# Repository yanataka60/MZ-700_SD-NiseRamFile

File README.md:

# MZ-700_SD+偽RAMFILE複合ボード

　しっぽいいんちょさんが作られた「偽RAMFILE for MZ-1500」を元にしてMZ-700_SDを合体させたボードです。

　オマケとしてMZ-1500のサウンド機能を付加してMZ-1500用ゲームのサウンドも鳴るようにしてみました。あくまでオマケですので完全にMZ-1500と同等になるかは未検証です。

#### 2026.4.17 Rev1.2の回路中LPFのコンデンサの位置に誤りがありました。後述「Rev1.2回路の修正」によりコンデンサの位置を修正してください。

#### 2026.4.25 Rev1.5以降では回路・基板改善しています。Rev1.2基板の場合のみ、後述「Rev1.2回路の修正」によりコンデンサの位置を修正してください。

#### 2026.6.21 MZ-700_SD+偽RAMFILE複合ボードに電源が供給されている状態でUSB-Cケーブルを接続してはいけない問題に対してRev1.6基板ではすーぱーたーぼさんからご指摘いただいた対策を施しました。Rev1.2、Rev1.5基板でも通常の使用でMZ-700_SD+偽RAMFILE複合ボードに電源が供給されている状態でUSB-Cケーブルを接続することはありませんので通常使用においてRev1.2、Rev1.5基板でも問題ありません。

　以下の機能があります。

・MZ-700_SDの起動及びMZ-700_SDの機能

・EMM0からの起動(ただし、EMM0にHu-BASICの起動ディスクイメージがある場合のみ)

・EMM0エミュレータ(320KByte)

・漢字ROMボードエミュレータ

・MZ-700のテキスト出力をエミュレートしてVGA出力

・VGA出力される出力にMZ-1500相当のPCG機能、パレット機能

・VGA出力される出力にPCG-700相当のPCG機能

・MZ-1500相当のサウンドエミュレート(SN76489x2、8253)

・EXT-ROM領域(E800h～FFFFh)のRAM化(起動時にはF000h～FFFFhにMZ-700_SD用ROMの内容が自動的に書き込まれます。1Z-009B_LauncherをLOAD起動後であればEXT-ROMをファイル化したEXT-ROM.MZTをEXT-ROM領域にLOADが可能です)

MZ-700_SD: https://github.com/yanataka60/MZ-700_SD

　「偽RAMFILE for MZ-1500」にはMZ-1R12 SRAMメモリエミュレータの機能がありますが、MZ-700_SDの起動用に使用しているのでMZ-1R12 SRAMメモリエミュレータとしての機能は使用できません。

　なおこの基板は、しっぽいいんちょさんの「偽1500 for MZ-700」のnise1500.uf2を書き込めば「偽1500 for MZ-700」になります。

　「偽1500 for MZ-700」とはフラッシュROMの使い方が違いますのでuf2ファイルを書き込んだときはそれぞれの説明に従ったフラッシュROMへの書込みを行ってください。

偽1500 for MZ-700:https://github.com/shippoiincho/nise1500

### (2026.8.13追記)すねいるさんのBARYONに対応するためArduinoプログラムを更新しました。また、ROMプログラムも合わせて更新することで多段ロードにも対応します。

### 多段ロードの詳細についてはMZ-80K_SDの「BARYON対応」「多段ロード対応」を参照してください。

　BARYON対応:https://github.com/yanataka60/MZ80K_SD#baryon%E5%AF%BE%E5%BF%9C2026813

　多段ロード対応:https://github.com/yanataka60/MZ80K_SD#%E5%A4%9A%E6%AE%B5%E3%83%AD%E3%83%BC%E3%83%89%E5%AF%BE%E5%BF%9C2026813

　Arduinoプログラム、ROMプログラムともMZ-80K_SD用に更新したものがそのまま使えます。

### BARYON起動時にE800h以降にも書き込み動作を行うようです。MZ-80K_SD、MZ-700_SDでは問題ありませんが、MZ-700_SD+偽RAMFILE複合ボードではE800h以降もRAM扱いとしていたため、SDアクセスルーチンが破壊されてしまいます。

### 当面、E800h以降はROM扱いに変更しましたのでRP2350Bフォルダにあるniseramfile.uf2でRP2350Bマイコンボードを書き換えてください。

## 回路図
　KiCadフォルダ内のMZ-700_SD+NRF.pdfを参照してください。

[回路図](https://github.com/yanataka60/MZ-700_SD-NiseRamFile/blob/main/KiCad/MZ-700_SD%2BNRF.pdf)

|番号|品名|数量|備考|
| ------------ | ------------ | ------------ | ------------ |
||J2、J5のいずれか|||
|J2|Micro_SD_Card_Kit|1|秋月電子通商 AE-microSD-LLCNV (注2)|
|J5|MicroSD Card Adapter|1|Arduino等に使われる5V電源に対応したもの(注4)|
|J3|コネクタ 2Pin|1|ピンヘッダで代用するときはGNDと間違えないよう1Pinで5Vだけにしたほうが良い|
|J4|DCジャック|1||
|J6,J7|ピンソケット2x15Pin|2|RP2350Bマイコンボード用,秋月電子通商 FHU-2x42SGなど|
|J8|VGA用基板ソケット 3列15ピン|1|マルツ DJ-VGA14.5など (注1)|
|J9|RCAジャック|1|秋月電子通商 MJ-523など|
|S1|3Pスライドスイッチ|1|秋月電子通商 SS12D01G4など|
|U1|74LS04|1||
|U3|8255|1||
|U4|Arduino_Pro_Mini_5V|1|Atmega328版を使用 168版は不可。(注3)|
|U6|74LS30|1||
||RP2350Bボード(Raspberry Pi Pico 2)|1|Amazon WA00021 RP2350Bマイコンボードなど|
|C1,C3,C5|積層セラミックコンデンサ 0.1uF|3||
|C2|積層セラミックコンデンサ 0.01uF|1||
|C6|電解コンデンサ 16v100uF|1||
|D1|ダイオード 1N5819|1||
|R1-R3|カーボン抵抗 330Ω|3||
|R4|カーボン抵抗 1kΩ|1||
||ピンヘッダ|2Pin分|Arduino_Pro_MiniにはA4、A5用のピンヘッダが付いていないため別途調達が必要です 秋月電子通商 PH-1x40SGなど|
||ピンソケット(任意)|26Pin分|Arduino_Pro_Miniを取り外し可能としたい場合に調達します 秋月電子通商 FHU-1x42SGなど|

　　　注1)VGA用基板ソケットには、ピン間隔の異なるものがあるようです。マルツ DJ-VGA14.5ではないものを購入する場合はこちらで寸法を確認してください。

　　　https://www.marutsu.co.jp/contents/shop/marutsu/datasheet/DJ-VGA14.5.pdf

　　　注2)秋月電子通商　AE-microSD-LLCNVのJ1ジャンパはショートしてください。

　　　注3)Arduino Pro MiniはA4、A5ピンも使っています。

　　　注4)MicroSD Card Adapterを使う場合

　　　　　J6に取り付けます。

　MicroSD Card Adapterについているピンヘッダを除去してハンダ付けするのが一番確実ですが、J6の穴にMicroSD Card Adapterをぴったりと押しつけ、裏から多めにハンダを流し込むことでハンダ付けをする方法もあります。なお、この方法の時にはしっかりハンダ付けが出来たかテスターで導通を確認しておいた方が安心です。

　ハンダ付けに自信のない方はJ5の秋月電子通商　AE-microSD-LLCNVをお使いください。AE-microSD-LLCNVならパワーLED、アクセスLEDが付いています。

## Rev1.2回路の修正(Rev1.2のみ、Rev1.5以降では修正しています)
　Rev1.2の回路に誤りがありました。LPF用コンデンサ(C2)を取り外し、0.01uFに変更の上、基板ハンダ面よりR4の出力側になるように取り付けてください。

## 偽RAMFILE for MZ-700の書込み
　RP2350Bフォルダにあるniseramfile.uf2をRP2350Bマイコンボードに書き込みます。

　RP2350BのBOOTボタンを押しながらUSB-Cケーブルを接続するとパソコンがUSBメディアとして認識しますのでniseramfile.uf2をドロップすると自動的に書き込まれます。

　書き込みが終了するとパソコンからはUSBとして見えなくなりますのでそうなったらケーブルを抜いて終了です。

### 書き込み(USB-Cケーブル接続)時の注意
#### Rev1.2基板、Rev1.5基板
　USB-Cケーブルを接続するときは、USB-C以外からMZ-700_SD+偽RAMFILE複合ボードに電源が供給されないようにしてください。

　MZ-700内部から内部電源として供給しているならMZ-700の電源は必ず切っておく、ACアダプタから外部電源として供給しているなら電源ジャックから外しておいてください。

　また、書き込み終わったらUSB-Cは必ず外してください。

#### Rev1.6基板
　対策済みです。USB-Cケーブルを接続するときにUSB-C以外からMZ-700_SD+偽RAMFILE複合ボードに電源が供給されていても問題は無くなっていますが、書き込むときにはUSB-Cケーブル以外から電源が供給されていない状態で行う方が無難です。

## MZ-700_SD用ROMプログラムの書き込み
~~MZ-700_SD/EMMフォルダ内のFD_rom1.bin又はFD_rom.binをRP2350BのフラッシュROMへ書き込みます。~~

~~https://github.com/yanataka60/MZ-700_SD/blob/main/EMM/FD_rom.BIN~~

(2026.8.13)多段ロード対応に伴い、MZ-80K_SDに統合しました。MZ-80K_SD/Z80フォルダ内のFD_rom.BINを使ってください。

https://github.com/yanataka60/MZ80K_SD/blob/main/Z80/FD_rom.BIN

　書き込みにはpicotool.exeが必要となります。以下のウェブページ右側の「Releases」からダウンロードできます。

https://github.com/raspberrypi/pico-sdk-tools

```
picotool.exe load -v -x FD_rom1.bin  -t bin -o 0x10080000
```

　また、EMM0に起動可能な内容(HuBASIC起動イメージ)があればEMMからの起動が可能です。

　EMMの内容をチェックしていないのでEMMが起動可能な内容(HuBASIC起動イメージ)でなかった場合には暴走しますのでご注意ください。

　EMM0からの起動は、MONITORから「FDE0」コマンドで起動できます。

## FONTファイルの書込み
　VGA出力を有効とするためにはMZ-700のフォントをRP2350Bに書き込む必要があります。

　MZ-700はソフトウェア的にフォントを取り出すすべがありませんが、疑似的に作り出す又はソフトウェアで読み出せるMZ-1500のFONTを使うなどの方法があります。Webで検索して作成してください。

　書き込みはpicotoolを使います。

```
picotool.exe load -v -x font.rom  -t bin -o 0x1001f000
```

## Arduinoプログラム
　MZ-80K_SDを参照してください。

https://github.com/yanataka60/MZ80K_SD?tab=readme-ov-file#arduino%E3%83%97%E3%83%AD%E3%82%B0%E3%83%A9%E3%83%A0

## 拡張機能の使い方
### MZ-700_SD(MZ-80K_SD)の起動
　MZ-700_SD(MZ-80K_SD)の起動方法、使用方法と同じです。

MZ-700_SD:https://github.com/yanataka60/MZ-700_SD

MZ-80K_SD:https://github.com/yanataka60/MZ80K_SD

### EMM0エミュレータ
　320KByteのEMM0として機能します。バッテリーバックアップ機能はなく、電源断で内容は消失します。

　ただし、バックアップ用のSlotが32個用意されているので電源断前にSlotに退避しておくことが可能です。

　また、Slot0の内容は電源投入又はIPL RESETした時にEMM0に自動的にコピーされるのであたかもバッテリーバックアップされていたかのような使い方が出来ます。

　EMMとSlotとのやり取りはI/Oポートから指示します。

#### SlotxxからEMM0への復帰
|アドレス|R/W|説明|
| ------------ | ------------ | ------------ |
|8Ch|W|指定したSlot番号(0～31)のSlotの内容をEMM0に復帰|

#### EMM0からSlotxxへの退避
|アドレス|R/W|説明|
| ------------ | ------------ | ------------ |
|8Dh|W|指定したSlot番号(0～31)のSlotへEMM0の内容を退避|

HuBASICからは以下のようになります。

```
OUT &H8C,0
```

```
OUT &H8D,0
```

　「EMM0」に起動可能なMZ-700用HuBASICが存在している場合、コマンド「FDE0」を実行することで「EMM0」のMZ-700用HuBASICから起動可能です。

　なお、EMMの00000番地が「01h」でなければEMMからの起動はせずにコマンド待ちに戻りますが、00000番地以降に異常があってもチェックはしていないので最悪暴走します。

　MZ-700用HuBASICは、テープ版しかなくそのままではEMMにHuBASICの起動イメージを作成することが出来ません。

　BouKiCHiさんのHuDiskなどを使いMZ-700用HuBASICの起動ディスクイメージを作成したうえでEMMMENUのEMMLOADでEMMに書き込む必要があります。

　EMMイメージを登録する場合はpicotoolから以下のようにします。

```
picotool.exe load -v -x EMM_image.bin  -t bin -o 0x10280000
```

### 漢字・辞書ROM MZ-1R13
　漢字・辞書ROM MZ-1R13から抽出したデータを登録します。

　抽出にはGET1R13を使いました。

http://fukui.s17.xrea.com/retro/mz2080b/mzgetkrom.html

　出来上がったファイルをpicotoolで登録します。

```
picotool.exe load -v -x MZ_1R13_DIC.ROM -t bin -o 0x10040000
```

```
picotool.exe load -v -x MZ_1R13.ROM  -t bin -o 0x10020000
```

## MZ-80K用ゲーム(アプリケーション)の実行
　FDL、FDコマンドでLOAD実行が可能です。アプリケーション内でのLOAD、SAVEには本体内ROMの書き換え、もしくはアプリケーションの書き換えが必要です。

　また、キーボードの違いによりそのまま動かないことがあります。

　詳しくは、MZ-80K_SDを参照してください。

https://github.com/yanataka60/MZ80K_SD

## MZ-700用ゲーム(アプリケーション)の実行
　FDL、FDコマンドでLOAD実行が可能です。アプリケーション内でのLOAD、SAVEにはアプリケーションを対応させる必要がある場合があります。

　詳しくは、MZ-80K_SDを参照してください。

https://github.com/yanataka60/MZ80K_SD

## MZ-1500用ゲーム(アプリケーション)の実行
　MZ-1500用ゲーム(アプリケーション)が動作するかもしれないのはあくまでもオマケです。動作したらラッキーぐらいでお願いします。

　なお、QD用ソフトは、事前にMZTファイル化しておいてください。

　また、アプリケーション内でLOAD、SAVEするにはMZ-1500_SDでアプリケーション内でのLOAD、SAVEに対応している必要があります。

　次の段階で試してみてください。

#### ①FDL、FDコマンドでLOAD実行。
　①で動いたもの

　　いぬふとさんのゲーム、PACKMAN、ICE BLOCK

#### ②多段LOADの場合は、FDL、FDコマンドでLOAD実行(PCG定義)。リセットして２段目をFDL、FDコマンドでLOAD実行(ゲーム本体)。
　②で動いたもの

　　DOORDOORmk2、FLAPPY、RALLY-X、ヴォルガード、DIGDUG、MAPPY、GALAGA、ドルアーガの塔(遊べますが外壁PCG定義が変です)

#### ③FDL、FDコマンドで1Z-009B_LauncherをLOAD実行し、1Z-009B_LauncherからFDL、FDコマンドでLOAD実行。
　③で動いたもの

　　サンダーフォース、BASIC MZ-5Z001(もしかしたら④の方が良いのかも)

#### ④FDL、FDコマンドで1Z-009B_LauncherをLOAD実行後、1Z-009B_LauncherからMZ-1500用EXT-ROM(E800h～FFFFh、実行アドレスE800h)をLOAD実行、MキーでMONITOR 9Z-502Mを起動したら「J0000」を実行して1Z-009B_Launcherに戻り、目的のアプリケーションをFDL、FDコマンドでLOAD実行。
　④で動いたもの

　　今のところ④が必要となったものには出会っていません。もしかしたらBASIC MZ-5Z001の機能のうち、EXT-ROMを必要とするものがあるかもしれません。

　　(2026.8.13追記)当面、E800h以降はROM扱いに変更しましたので④は使えなくなります。

### 1Z-009B_Launcherの作り方
　1Z-009B_Launcherフォルダにある1Z-009B_SD.mzt(2630Byte)の後ろにMZ-1500実機から抽出した1Z-009B MONITOR(0000h～0FFFh)をバイナリエディタなどで連結して保存してください。

　6627Byteのファイルになります。

　(2026.8.15追記)1Z-009B_Launcherも多段ロード対応にさせました。ただし今のところ1Z-009B_Launcherを使うのは③の場合のみですので使う場面はありません。

### MZ-1500用EXT-ROMファイルの作り方

(2026.8.15追記)E800h以降をROM扱いに変更しましたのでLOAD出来なくなりました。

　MZ-1500実機からEXT-ROM(E800h～FFFFh)までを抽出してバイナリファイルとしたうえでヘッダを付加してmztファイルとしてください。

　この時、実行アドレスをE800hとしておきます。

### MZ-700_SD+偽RAMFILE複合ボード対応BASIC MZ-5Z001
　前述「MZ-1500用ゲーム(アプリケーション)の実行」の③又は④でBASIC MZ-5Z001は実行可能ですが、SDを使用するにはSD用パッチあてが必要です。

　MZ-1500_SDとMZ-700_SDではArudinoをコントロールする8255のI/Oアドレスに違いがあり、MZ-1500_SD対応パッチを当てたBASIC MZ-5Z001はそのままでは使えないのでバイナリエディタで以下の修正を行ってください。

　「BASIC 1Z-5Z001-SD.MZT」(AUTORUN未対応版 42581Byte)
|MZTアドレス|修正前|修正後|
| ------------ | ------------ | ------------ |
|A30F|A3|DB|
|A313|A0|D8|
|A315|A2|DA|
|A31B|A1|D9|
|A320|A3|DB|
|A327|A3|DB|
|A33C|A0|D8|
|A340|A3|DB|
|A347|A3|DB|
|A34D|A2|DA|
|A354|A2|DA|

　「BASIC 1Z-5Z001-SD-AUTORUN.MZT」(AUTORUN対応版 42592Byte)
|MZTアドレス|修正前|修正後|
| ------------ | ------------ | ------------ |
|A31A|A3|DB|
|A31E|A0|D8|
|A320|A2|DA|
|A326|A1|D9|
|A32B|A3|DB|
|A332|A3|DB|
|A347|A0|D8|
|A34B|A3|DB|
|A352|A3|DB|
|A358|A2|DA|
|A35F|A2|DA|

## 専用トレイとカバー
　専用トレイとカバーを作ってみました。

　STLフォルダにあるSTLファイルを使ってください。

　トレイはCMTユニットを引っ掛ける手前のツメの下に潜り込ませるように入れます。

　カバーは手前からかぶせてツメに引っ掛けます。

　カバーを外すときは背面からトレイごと持ち上げるようにすると外れます。

　カバー内は、RP2350Bがギリギリ入る高さ16mmほどです。Arduino、SDカードユニットにソケットを使うときはその高さに収まる背の低いタイプを使ってください。

## 開発環境、使用ライブラリなど
　開発環境は、Visual Studio Codeです。

　VGAライブラリは以下を使用しています。

- [VGA ライブラリ(一部改変)](https://github.com/vha3/Hunter-Adams-RP2040-Demos/tree/master/VGA_Graphics)

## 謝辞
　素晴らしい拡張モジュールを開発し、自由に改変・公開を快く承諾してくださったしっぽいいんちょさん、ありがとうございました。

## 追記
2026.4.17 Rev1.2回路でLPFのコンデンサの位置に誤りがありました。すーぱーたーぼさん、ご指摘ありがとうございます。

2026.4.18 書き込み(USB-Cケーブル接続)時の注意を追記しました。

2026.4.25 Rev1.5を公開しました。

2026.4.30 トレイとカバーのSTLファイルを追加しました。
          MZ-700_SD+偽RAMFILE複合ボード対応BASIC MZ-5Z001にするための修正点を追記。

2026.6.21 MZ-700_SD+偽RAMFILE複合ボードに電源が供給されている状態でUSB-Cケーブルを接続してはいけない問題に対してすーぱーたーぼさんからご指摘いただいた対策を施しました。

2026.8.13 BARYONに対応しました。retrogamer128さんの要望により多段ロードに対応しました。

2026.8.15 1Z-009B_Launcherも多段ロード対応としました。

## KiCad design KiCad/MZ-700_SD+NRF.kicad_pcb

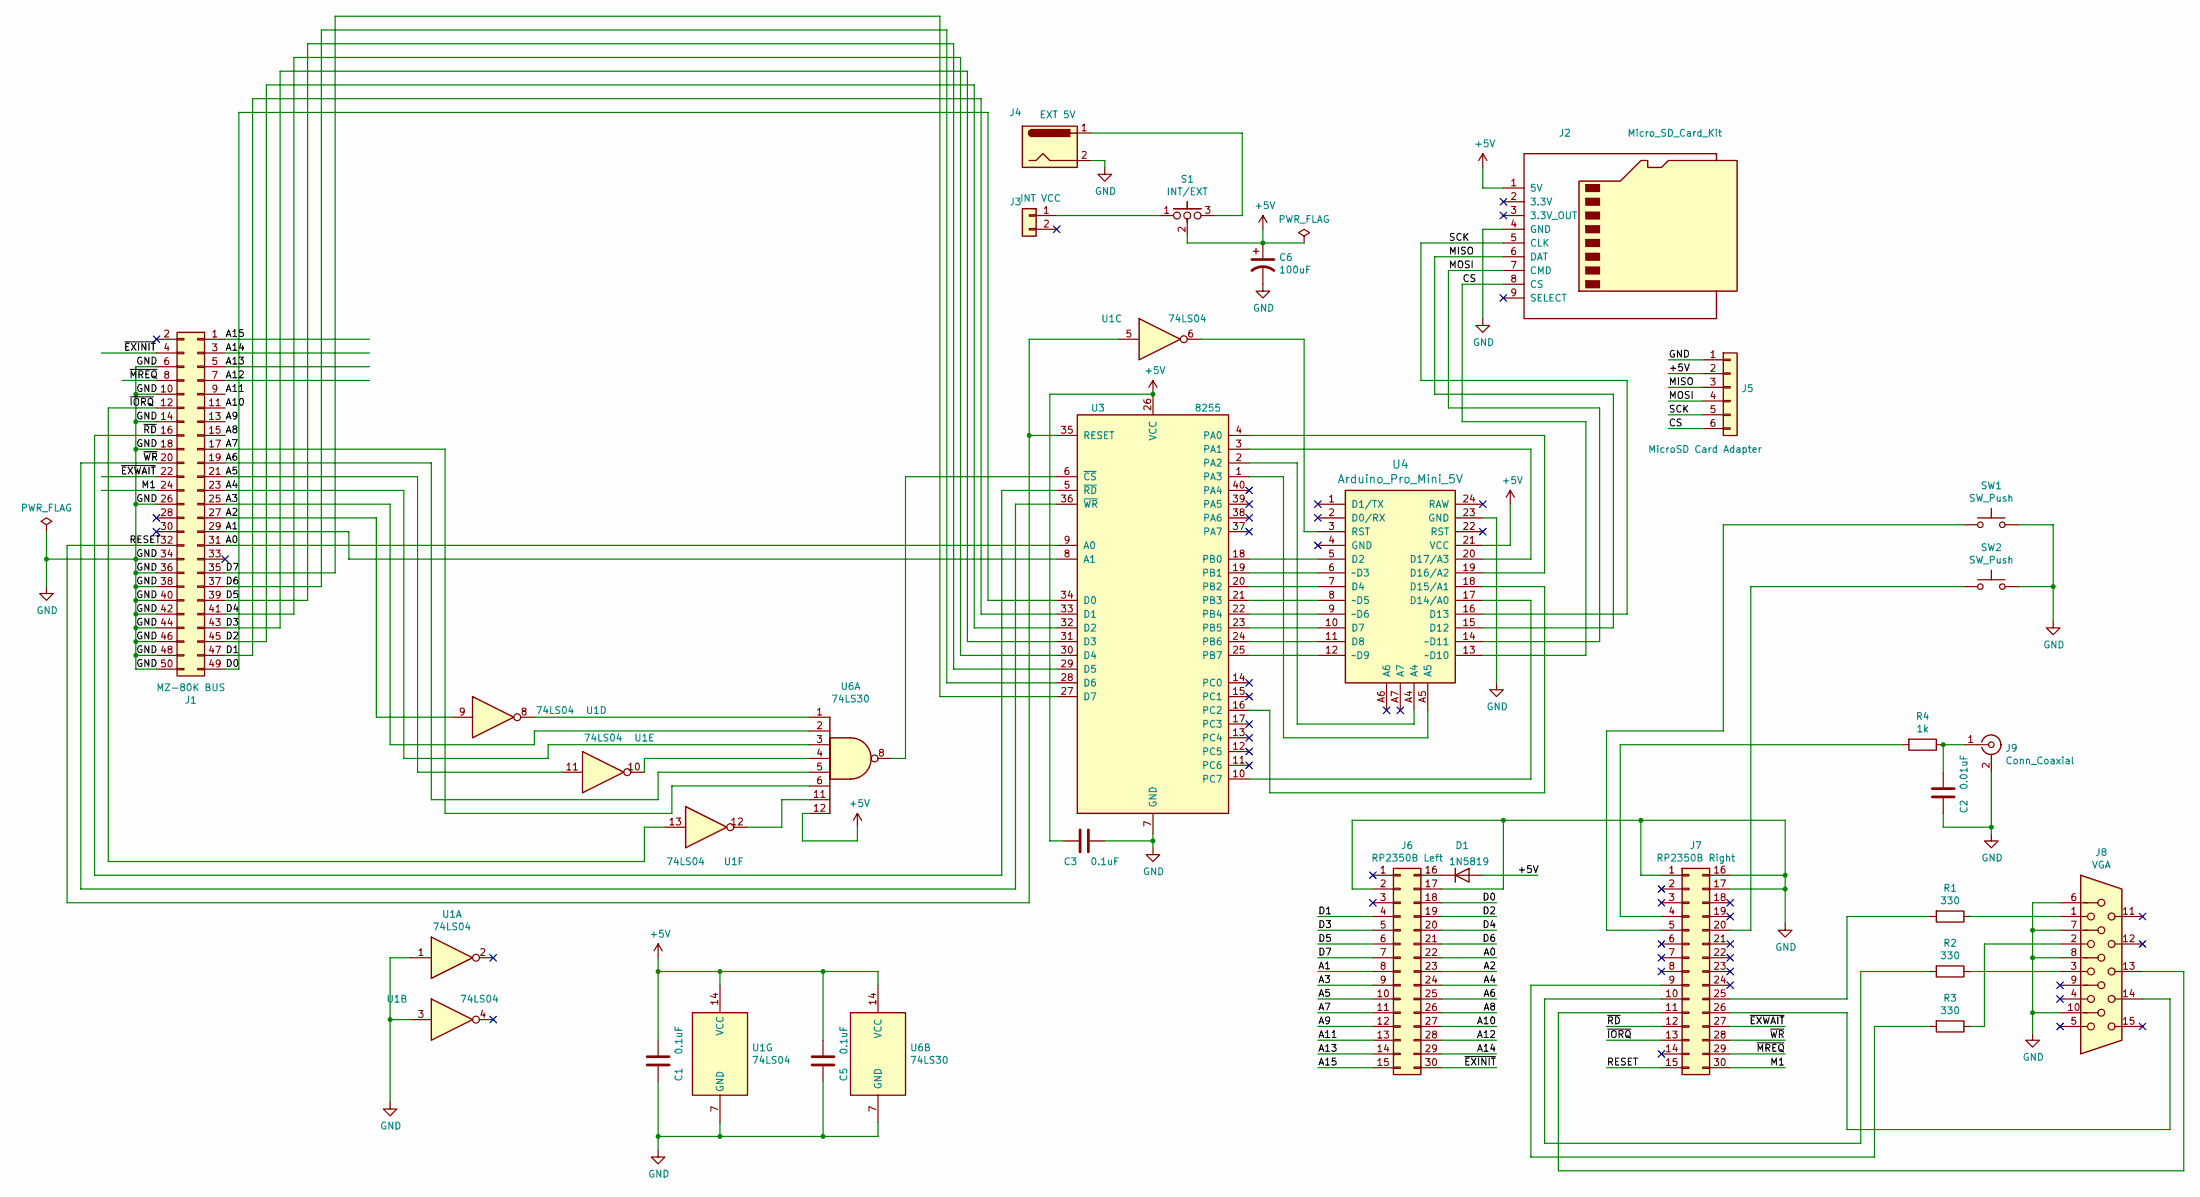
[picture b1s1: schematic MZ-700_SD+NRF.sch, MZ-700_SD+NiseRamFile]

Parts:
C1, C3, C5: 0.1uF; C_Rect_L4.0mm_W2.5mm_P2.50mm
C2: 0.01uF; C_Rect_L4.0mm_W2.5mm_P2.50mm
C6: 100uF; CP_Radial_D5.0mm_P2.50mm
D1: 1N5819; D_DO-41_SOD81_P10.16mm_Horizontal
J1: MZ-80K BUS; PinSocket_2x25_P2.54mm_Horizontal
J2: Micro_SD_Card_Kit; AE-microSD-LLCNV
J3: INT VCC; PinHeader_1x02_P2.54mm_Horizontal
J4: EXT 5V; BarrelJack_Horizontal
J5: MicroSD Card Adapter; PinSocket_1x06_P2.54mm_Vertical
J6: RP2350B Left; PinHeader_2x15_P2.54mm_Vertical
J7: RP2350B Right; PinHeader_2x15_P2.54mm_Vertical
J8: VGA; DSUB-15-HD_Female_Horizontal_P2.29x1.98mm_EdgePinOffset3.03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
J9: Conn_Coaxial; RCAConAE
R1, R2, R3: 330; R_Axial_DIN0207_L6.3mm_D2.5mm_P7.62mm_Horizontal
R4: 1k; R_Axial_DIN0207_L6.3mm_D2.5mm_P7.62mm_Horizontal
S1: INT/EXT; PinHeader_1x03_P2.54mm_Vertical
SW1, SW2: SW_Push; SW_PUSH_6mm_H4.3mm
U1: 74LS04; DIP-14_W7.62mm_LongPads
U3: 8255; DIP-40_W15.24mm_LongPads
U4: Arduino_Pro_Mini_5V; Arduino_Pro_Mini
U6: 74LS30; DIP-14_W7.62mm_LongPads

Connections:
+5V: C1.2, C3.1, C5.2, C6.1, D1.2 (A), J2.1 (5V), J5.2, S1.2, U1.14 (VCC), U3.26 (VCC), U4.21 (VCC), U6.12, U6.14 (VCC)
/A0: J1.31, J6.22, U3.9 (A0)
/A1: J1.29, J6.8, U3.8 (A1)
/A2: J1.27, J6.23, U1.9
/A3: J1.25, J6.9, U6.2
/A4: J1.23, J6.24, U6.3
/A5: J1.21, J6.10, U1.11
/A6: J1.19, J6.25, U6.5
/A7: J1.17, J6.11, U6.6
/A8: J1.15, J6.26
/A9: J1.13, J6.12
/A10: J1.11, J6.27
/A11: J1.9, J6.13
/A12: J1.7, J6.28
/A13: J1.5, J6.14
/A14: J1.3, J6.29
/A15: J1.1, J6.15
/CS: J2.8 (CS), J5.6, U4.13 (~~D10)
/D0: J1.49, J6.18, U3.34 (D0)
/D1: J1.47, J6.4, U3.33 (D1)
/D2: J1.45, J6.19, U3.32 (D2)
/D3: J1.43, J6.5, U3.31 (D3)
/D4: J1.41, J6.20, U3.30 (D4)
/D5: J1.39, J6.6, U3.29 (D5)
/D6: J1.37, J6.21, U3.28 (D6)
/D7: J1.35, J6.7, U3.27 (D7)
/M1: J1.24, J7.30
/MISO: J2.6 (DAT), J5.3, U4.15 (D12)
/MOSI: J2.7 (CMD), J5.4, U4.14 (~~D11)
/RESET: J1.32, J7.15, U1.5, U3.35 (RESET)
/SCK: J2.5 (CLK), J5.5, U4.16 (D13)
/~EXINIT: J1.4, J6.30
/~EXWAIT: J1.22, J7.27
/~IORQ: J1.12, J7.13, U1.13
/~MREQ: J1.8, J7.29
/~RD: J1.16, J7.12, U3.5 (~RD~)
/~WR: J1.20, J7.28, U3.36 (~WR~)
GND: C1.1, C2.1, C3.2, C5.1, C6.2, J1.6, J1.10, J1.14, J1.18, J1.26, J1.34, J1.36, J1.38, J1.40, J1.42, J1.44, J1.46, J1.48, J1.50, J2.4 (GND), J4.2, J5.1, J6.2, J6.17, J7.1, J7.16, J7.17, J8.6, J8.7, J8.8, J8.10, J9.2 (Ext), SW1.2, SW2.2, U1.1, U1.3, U1.7 (GND), U3.7 (GND), U4.23 (GND), U6.7 (GND)
unnamed: C2.2, J9.1 (In), R4.1
unnamed: D1.1 (K), J6.16
unnamed: J3.1, S1.1
unnamed: J4.1, S1.3
unnamed: J7.4, R4.2
unnamed: J7.5, SW1.1
unnamed: J7.9, R3.2
unnamed: J7.10, R2.2
unnamed: J7.11, J8.13
unnamed: J7.20, SW2.1
unnamed: J7.25, R1.2
unnamed: J7.26, J8.14
unnamed: J8.1, R1.1
unnamed: J8.2, R3.1
unnamed: J8.3, R2.1
unnamed: U1.6, U4.3 (RST)
unnamed: U1.8, U6.1
unnamed: U1.10, U6.4
unnamed: U1.12, U6.11
unnamed: U3.1 (PA3), U4.A5
unnamed: U3.2 (PA2), U4.A4
unnamed: U3.3 (PA1), U4.20 (D17/A3)
unnamed: U3.4 (PA0), U4.19 (D16/A2)
unnamed: U3.6 (~CS~), U6.8
unnamed: U3.10 (PC7), U4.17 (D14/A0)
unnamed: U3.16 (PC2), U4.18 (D15/A1)
unnamed: U3.18 (PB0), U4.5 (D2)
unnamed: U3.19 (PB1), U4.6 (~~D3)
unnamed: U3.20 (PB2), U4.7 (D4)
unnamed: U3.21 (PB3), U4.8 (~~D5)
unnamed: U3.22 (PB4), U4.9 (~~D6)
unnamed: U3.23 (PB5), U4.10 (D7)
unnamed: U3.24 (PB6), U4.11 (D8)
unnamed: U3.25 (PB7), U4.12 (~~D9)

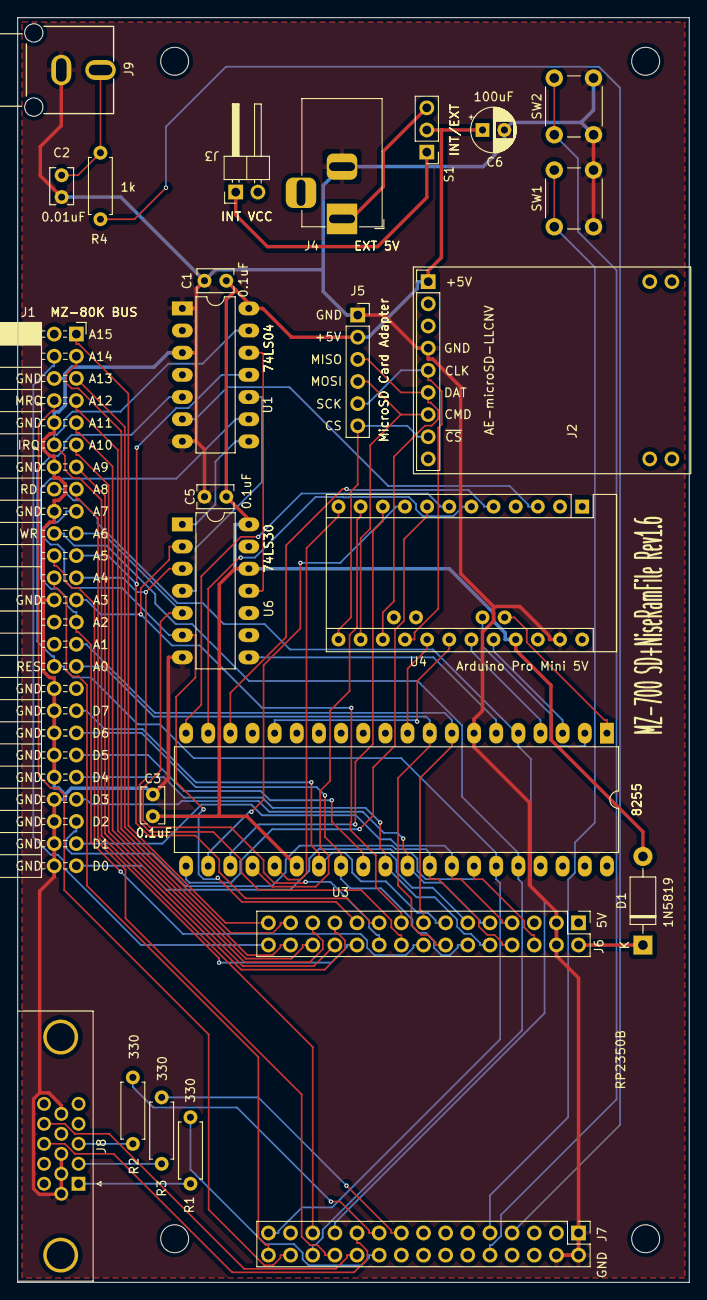
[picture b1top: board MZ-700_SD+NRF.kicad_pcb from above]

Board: 2 copper layers, 77.0 x 145.0 mm, 30 parts (0 on the bottom side), 72 nets.

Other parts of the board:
MH1, MH2, MH3, MH4: MountingHole_3.2mm_M3

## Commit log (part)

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2026-04-13 Create Kicad
